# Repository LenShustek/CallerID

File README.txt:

Caller ID display

   This is the software for a small box that displays the caller ID information generated
   by the ethernet version of the "Whozz Calling?"(tm) multi-line caller ID hardware.
   See https://www.callerid.com/.

   Our display box, measuring 4.4" x 2.3" x 1.1" and powered by a USB wall-wart, contains:
      - a 4-line 20-character display
      - two pushbuttons for scrolling the display up and down
      - an Adafruit Feather Huzzah ESP8266 processor with WiFi

   The box receives, over WiFi, the call information that is broadcast by the WhoozCalling
   hardware for up to 8 phone lines. Multiple display boxes can be deployed and will display
   the same information. Each box records up to 200 calls while it is powered on.

   The most recent 70 calls (although without call duration) are kept in
   non-volatile memory and are reloaded into the display if the box is restarted.
   (In the code we call the non-volatile memory EEPROM, but it's implemented as
   one block of the FLASH memory that is written all at once.)

   There are several pieces of configuration information to set up:
     - the SSID of the WiFi network
     - the password for the WiFi network
     - the names to be displayed for lines 1 through 8
     - whether the backlight should be turned off when idle

   The configuration information is requested if it has never been set, or
   if both buttons are pushed at the same time and then released.

   The configuration strings can be set, painfully, using the two pushbuttons.
   The top button cycles through choices for a character, and the bottom button
   goes to the next character, or to the next configuration string.

   But you can also use a computer keyboard to set configuration strings as follows:
     - plug the device into a USB port of your computer
     - run a terminal emulator program set to 9600 baud
        (For PuTTY on Windows: choose a "Serial" connection line like "COM27"
     - type each name asked for, with "Enter" signaling done. Backspace works.

   The packet format is not thoroughly documented by Whozz Calling, so there may be 
   some I don't understand that generate a "bad packet" message. Pushing both
   buttons for more than three seconds and then releasing will display the contents
   of the last such puzzling packet so we can add a decode for it.
   
   Len Shustek
   April 2019

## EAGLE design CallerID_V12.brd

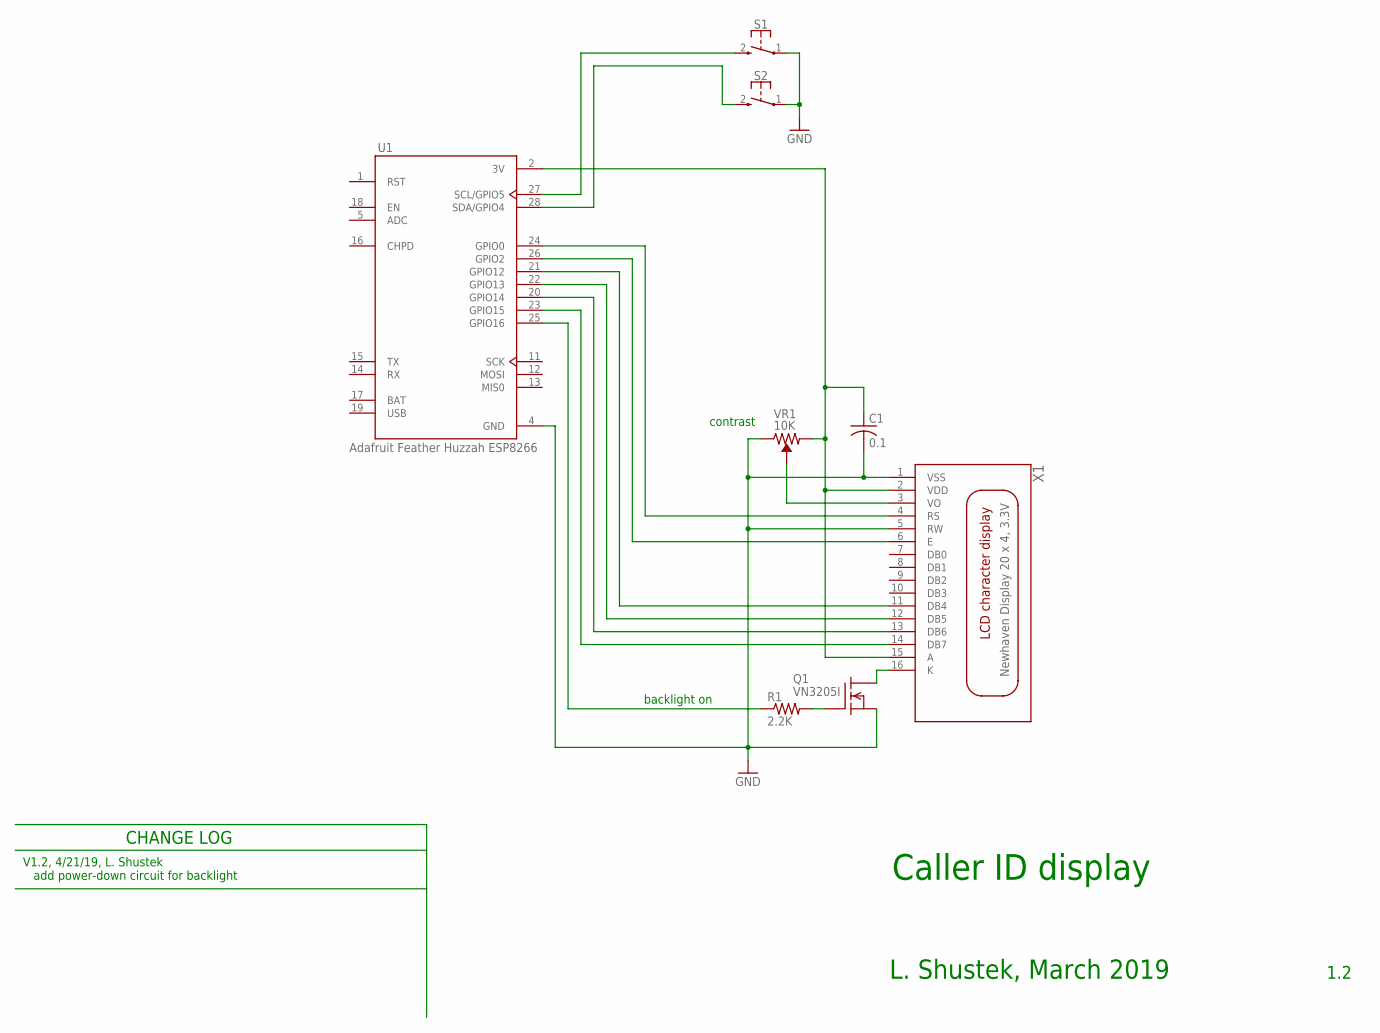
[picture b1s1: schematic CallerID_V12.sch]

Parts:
C1: 0.1; C050-024X044
Q1: VN3205I; TO92-INLINE
R1: 2.2K; 0207/10
S1, S2: PUSHBUTTON-SPST
U1: Adafruit Feather Huzzah ESP8266; ADAFRUIT-FEATHER-WIFI
VR1: 10K; TRIMBOT-BOURNS-3362M
X1: Newhaven Display 20 x 4, 3.3V; LCD-CHARACTER-DISPLAY-20X4-NEWHAVEN

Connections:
GND: C1.2, Q1.1 (S), S1.1, S2.1, U1.4 (GND), VR1.3 (CW), X1.1 (VSS), X1.5 (RW)
unnamed: VR1.2 (WIPER), X1.3 (VO)
unnamed: Q1.3 (D), X1.16 (K)
unnamed: S1.2 (3), U1.27 (SCL/GPIO5)
unnamed: S2.2 (3), U1.28 (SDA/GPIO4)
unnamed: U1.23 (GPIO15), X1.14 (DB7)
unnamed: U1.20 (GPIO14), X1.13 (DB6)
unnamed: U1.22 (GPIO13), X1.12 (DB5)
unnamed: U1.21 (GPIO12), X1.11 (DB4)
unnamed: U1.26 (GPIO2), X1.6 (E)
unnamed: U1.24 (GPIO0), X1.4 (RS)
unnamed: R1.1, U1.25 (GPIO16)
unnamed: Q1.2 (G), R1.2
VDD: C1.1, U1.2 (3V), VR1.1 (CCW), X1.2 (VDD), X1.15 (A)

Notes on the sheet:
Caller ID display
L. Shustek, March 2019
1.2
contrast
CHANGE LOG
V1.2, 4/21/19, L. Shustek add power-down circuit for backlight
backlight on

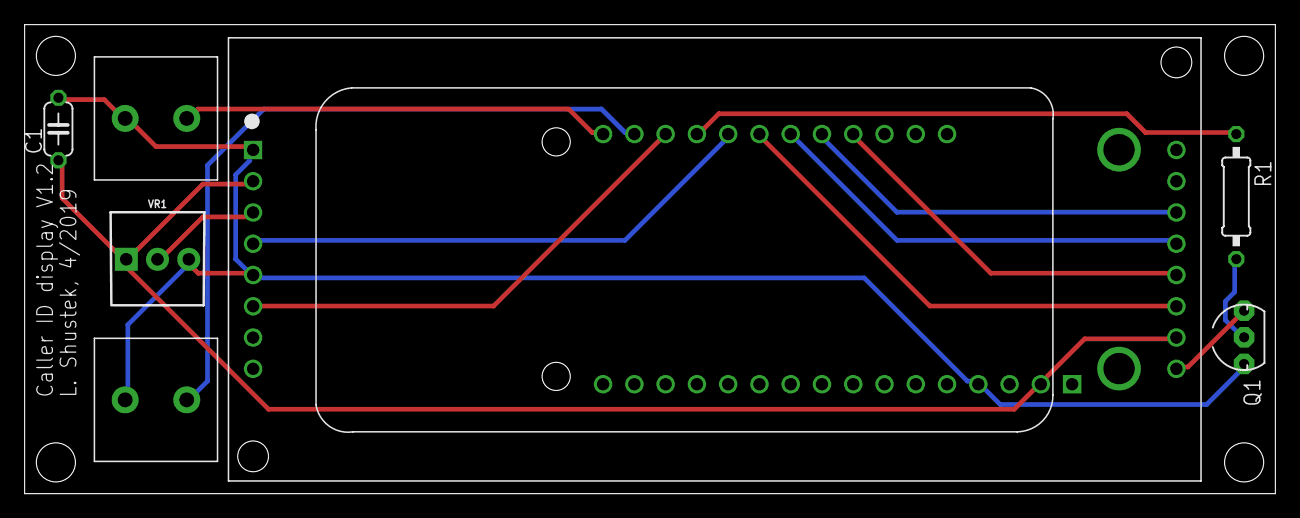
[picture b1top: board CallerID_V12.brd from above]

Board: 2 copper layers, 101.6 x 38.1 mm, 8 parts (1 on the bottom side), 14 nets.

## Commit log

2019-04-20 first release
2019-04-22 Add backlight dimming option
2019-06-25 decode type Bn packets
